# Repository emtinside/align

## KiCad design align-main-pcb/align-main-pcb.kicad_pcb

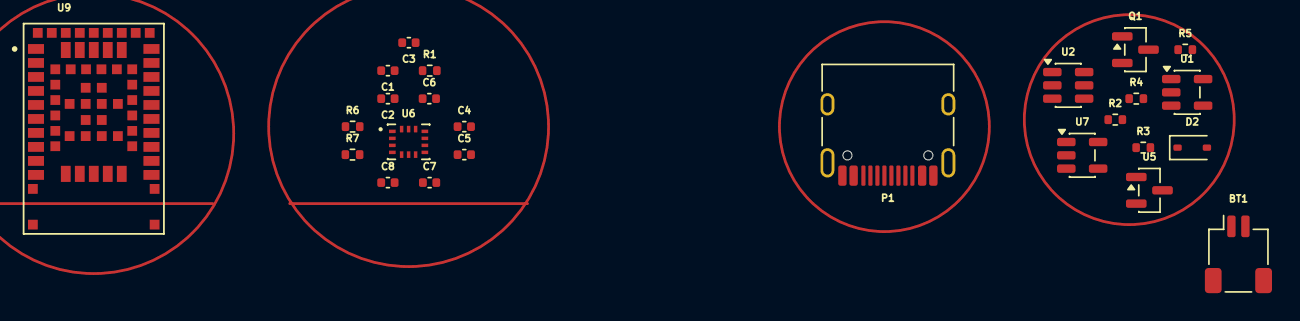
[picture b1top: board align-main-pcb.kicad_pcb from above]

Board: 2 copper layers, 25 parts (0 on the bottom side), 18 nets, no tracks yet.

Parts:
BT1: 3.85V; JST_SH_SM02B-SRSS-TB_1x02-1MP_P1.00mm_Horizontal
C1, C4: 1uF; C_0402_1005Metric
C2, C3: 10uF; C_0402_1005Metric
C5, C6: 4.7uF; C_0402_1005Metric
C7, C8: 100nF; C_0402_1005Metric
D2: D_Schottky; D_SOD-323
P1: USB_C_Plug_USB2.0; USB_C_Receptacle_HRO_TYPE-C-31-M-12
Q1: DMG2301L; SOT-23
R1, R2, R3: 100k; R_0402_1005Metric
R4: 2k; R_0402_1005Metric
R5: 470; R_0402_1005Metric
R6, R7: 4.7k; R_0402_1005Metric
U1: MCP73831-2-OT; SOT-23-5
U2: TPS22917DBV; SOT-23-6
U5: TPS3839DBZ; SOT-23
U6: BMI270; XDCR_BMI270
U7: TPS7A20xxxDBV; SOT-23-5
U9: NINA-B306-00B-00; XCVR_NINA-B306-00B-00

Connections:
3V3: C2.1, C7.1, C8.1, R6.2, R7.2, U6.5 (VDDIO), U6.8 (VDD), U6.12 (CSB), U7.5 (OUT)
/BAT_SIG: R2.2, R3.1
/USB_DM: P1.A7 (D-), U9.55 (USB_DM)
/USB_DP: P1.A6 (D+), U9.54 (USB_DP)
BMI270_INT1: U6.4 (INT1), U9.46 (TRACE_D1/GPIO_46)
BMI270_INT2: U6.9 (INT2), U9.50 (QSPI_D0/GPIO_50)
EAGP: U9.EAGP1 (EAGP), U9.EAGP2 (EAGP), U9.EAGP3 (EAGP), U9.EAGP4 (EAGP)
EGP: U9.EGP1 (EGP), U9.EGP2 (EGP), U9.EGP3 (EGP), U9.EGP4 (EGP), U9.EGP5 (EGP), U9.EGP6 (EGP), U9.EGP7 (EGP), U9.EGP8 (EGP), U9.EGP9 (EGP), U9.EGP10 (EGP), U9.EGP11 (EGP), U9.EGP12 (EGP)
GND: BT1.2 (-), C1.2, C2.2, C3.2, C4.2, C5.2, C6.2, C7.2, C8.2, P1.A1 (GND), P1.A12 (GND), P1.B1 (GND), P1.B12 (GND), R1.2, R3.2, R4.2, U2.2 (GND), U5.1 (GND), U6.1 (SDO), U6.6 (GNDIO), U6.7 (GND), U7.2 (GND), U9.6 (GND), U9.12 (GND), U9.14 (GND), U9.26 (GND), U9.30 (GND), U9.53 (GND)
unnamed: R4.1, U1.2 (V_{SS}), U1.5 (PROG)
unnamed: R5.2, U1.1 (STAT)
unnamed: R2.1, U2.6 (VOUT)
unnamed: U5.2 (~RESET), U7.3 (EN)
SCL: R6.1, U6.13 (SCX), U9.3 (GPIO_3)
SDA: R7.1, U6.14 (SDX), U9.2 (GPIO_2)
VBAT: BT1.1 (+), C4.1, C5.1, Q1.2 (S), U1.3 (V_{BAT}), U2.1 (VIN)
VSYS: C1.1, C3.1, D2.1 (K), Q1.3 (D), U5.3 (VDD), U7.1 (IN), U9.10 (VCC)
VUSB: C6.1, D2.2 (A), P1.A4 (VBUS), P1.A9 (VBUS), P1.B4 (VBUS), P1.B9 (VBUS), Q1.1 (G), R1.1, U1.4 (V_{DD}), U9.19 (~RESET)
